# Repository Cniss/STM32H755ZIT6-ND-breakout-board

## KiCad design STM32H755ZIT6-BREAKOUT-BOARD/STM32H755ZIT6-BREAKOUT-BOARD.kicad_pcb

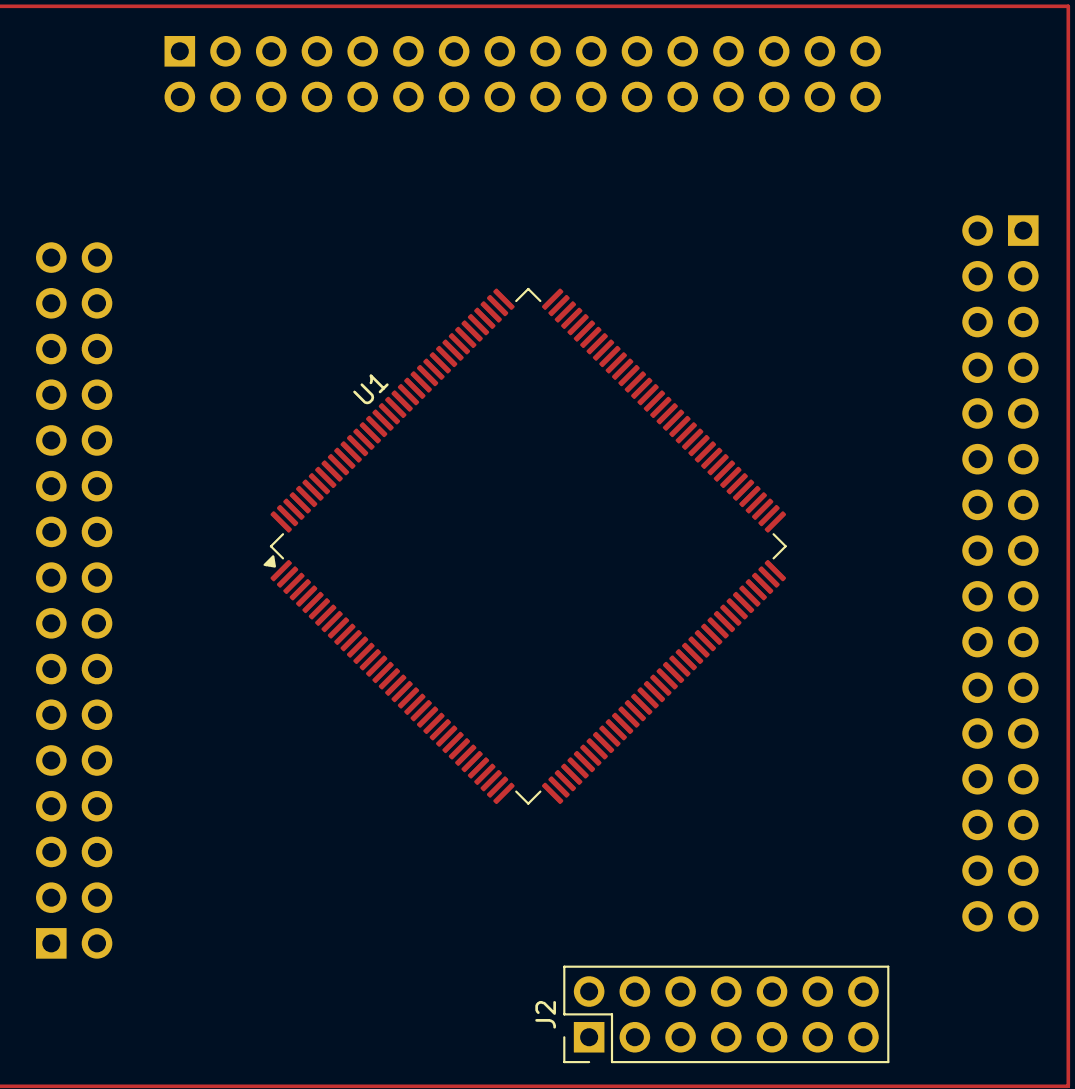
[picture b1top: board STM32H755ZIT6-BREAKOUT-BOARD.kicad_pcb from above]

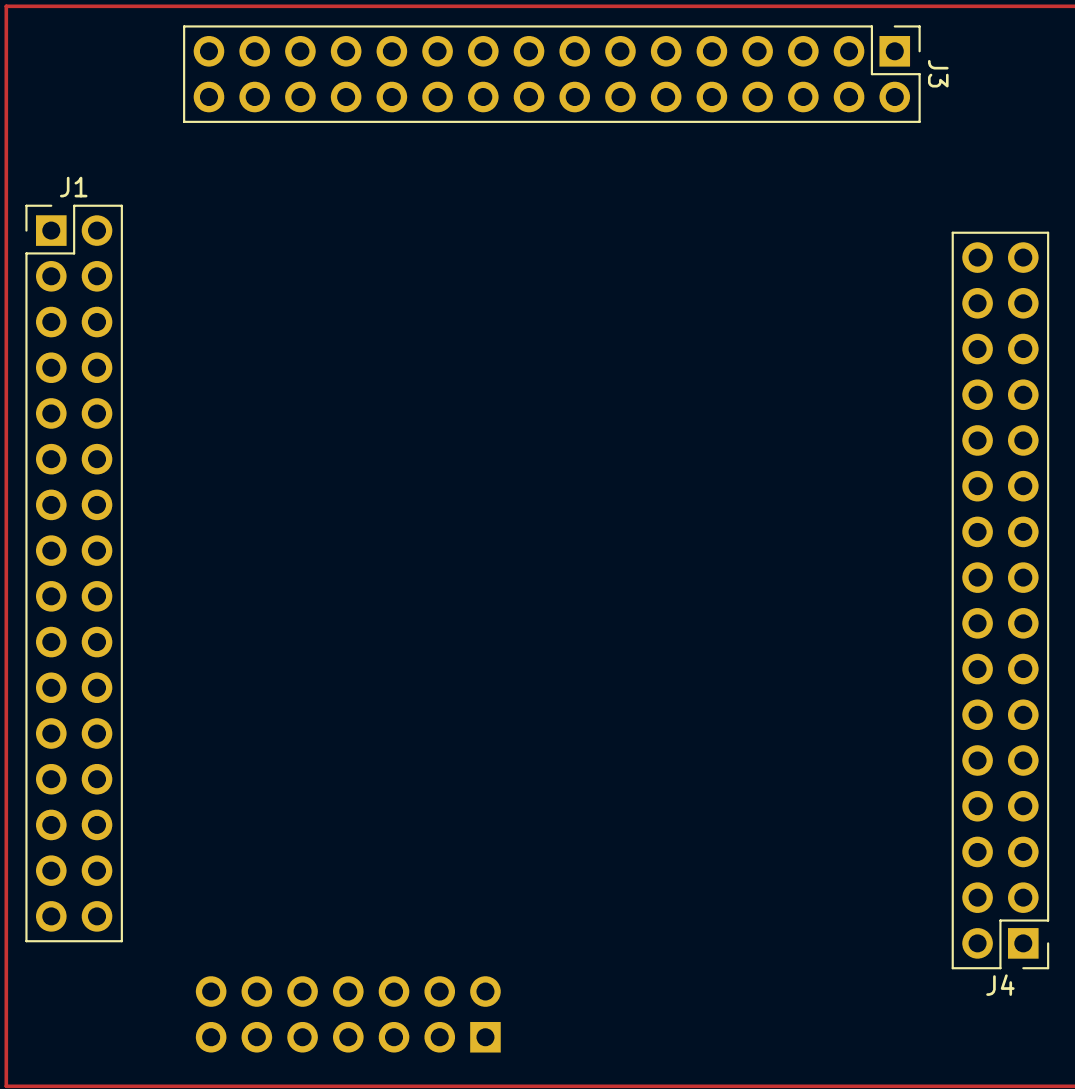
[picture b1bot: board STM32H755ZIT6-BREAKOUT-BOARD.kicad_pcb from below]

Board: 2 copper layers, 5 parts (3 on the bottom side), 5 nets, no tracks yet.

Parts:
J1, J3, J4: Conn_02x16_Odd_Even; PinHeader_2x16_P2.54mm_Vertical
J2: Conn_ST_STDC14; PinHeader_2x07_P2.54mm_Vertical
U1: STM32H755ZITx; LQFP-144_20x20mm_P0.5mm

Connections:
+3.3V: J2.3 (VCC), U1.7 (VDD), U1.8 (VBAT), U1.13 (VDD), U1.16 (VDDSMPS), U1.19 (VDD), U1.32 (VDD), U1.42 (VDD), U1.56 (VDD), U1.71 (VDD), U1.79 (VDD), U1.92 (VDD), U1.106 (VDD), U1.119 (VDD), U1.129 (VDD), U1.144 (VDD)
/JTDO/SWO: U1.107 (PA14), U1.130 (PB3)
/VCAP1: U1.68 (VCAP), U1.103 (VCAP), U1.140 (VCAP)
/VDDLDO: U1.17 (VFBSMPS), U1.70 (VDDLDO), U1.105 (VDDLDO), U1.143 (VDDLDO)
GND: J2.5 (GND), J2.7 (GND), J2.11 (GNDDetect), U1.6 (VSS), U1.12 (VSS), U1.14 (VSSSMPS), U1.18 (VSS), U1.33 (VSS), U1.34 (VSSA), U1.41 (VSS), U1.55 (VSS), U1.69 (VSS), U1.80 (VSS), U1.89 (VSS), U1.104 (VSS), U1.118 (VSS), U1.128 (VSS), U1.141 (VSS)

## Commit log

2025-10-25 Schematic work
2025-10-25 more schematic
2025-10-25 schematic pin labels
2025-10-25 crystal calculation
2025-10-26 pinheaders
2025-10-27 edited internal SMPS
